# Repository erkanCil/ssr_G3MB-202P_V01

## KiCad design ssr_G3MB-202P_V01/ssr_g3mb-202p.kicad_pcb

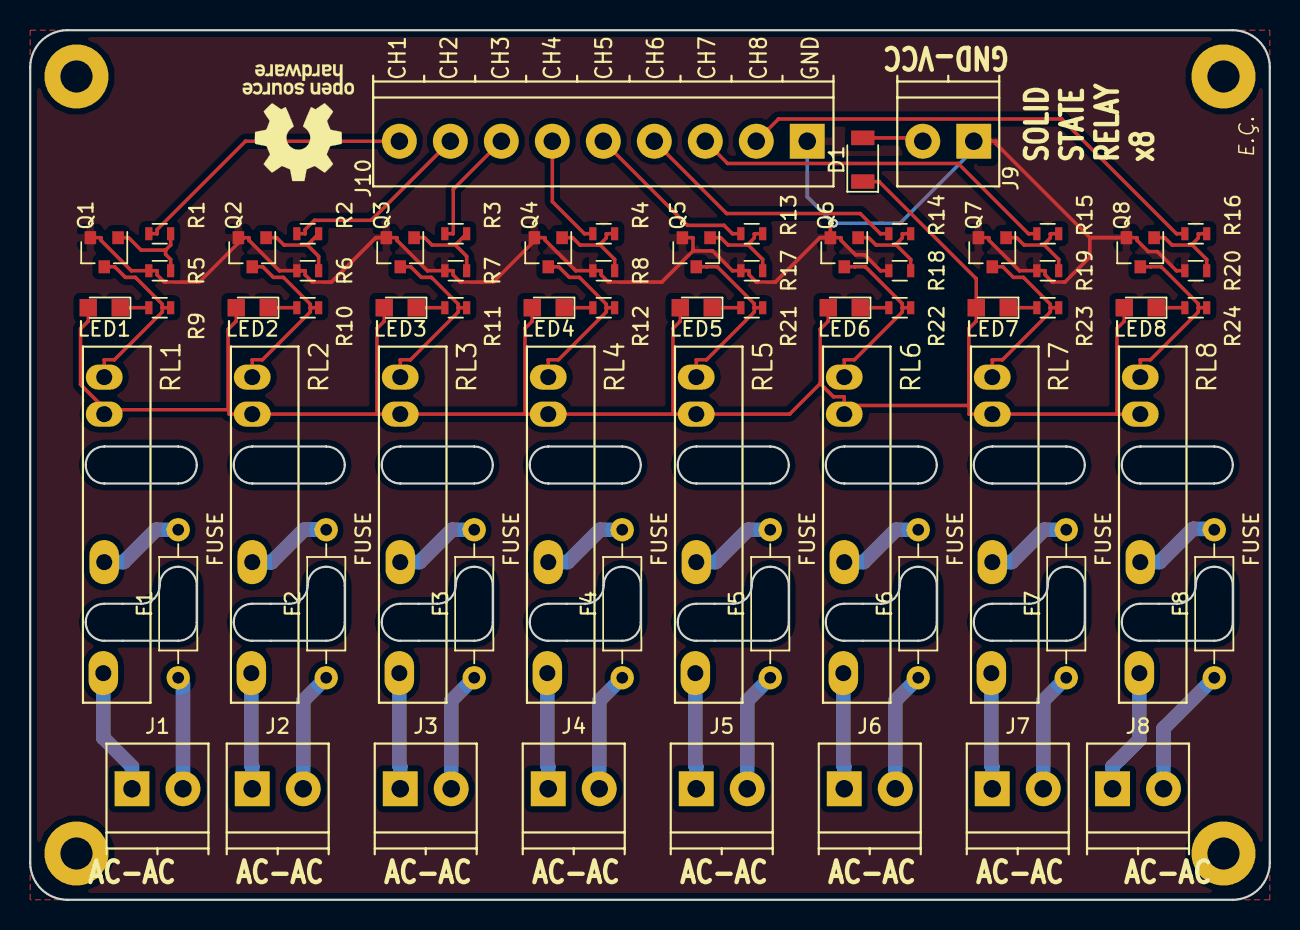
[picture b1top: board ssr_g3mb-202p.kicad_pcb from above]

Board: 2 copper layers, 85.1 x 59.7 mm, 71 parts (0 on the bottom side), 59 nets.

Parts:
D1: SM4001; D_1206
F1, F2, F3, F4, F5, F6, F7, F8: Fuse; R_Axial_DIN0207_L6.3mm_D2.5mm_P10.16mm_Horizontal
J1, J2, J3, J4, J5, J6, J7, J8, J9: Screw_Terminal_01x02; TerminalBlock_Pheonix_PT-3.5mm_2pol
J10: Screw_Terminal_01x09; TerminalBlock_Pheonix_PT-3.5mm_9pol
LED1, LED2, LED3, LED4, LED5, LED6, LED7, LED8: LED; LED_0805
Q1, Q2, Q3, Q4, Q5, Q6, Q7, Q8: MMBT3904/SOT23; SOT-23
R1, R2, R3, R4, R13, R14, R15, R16: 3K3; R_0603
R5, R6, R7, R8, R17, R18, R19, R20: 10K; R_0603
R9, R10, R11, R12, R21, R22, R23, R24: 1K; R_0603
REF1, REF2, REF3, REF4: MountingHole_2.2mm_M2_Pad
RL1, RL2, RL3, RL4, RL5, RL6, RL7, RL8: SSR_G3MB-202P; G3MB-202P

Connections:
+5V: D1.1, LED1.2, LED2.2, LED3.2, LED4.2, LED5.2, LED6.2, LED7.2, LED8.2, RL1.3, RL2.3, RL3.3, RL4.3, RL5.3, RL6.3, RL7.3, RL8.3
/CH1: J10.9, R1.2
/CH2: J10.8, R2.2
/CH3: J10.7, R3.2
/CH4: J10.6, R4.2
/CH5: J10.5, R13.2
/CH6: J10.4, R14.2
/CH7: J10.3, R15.2
/CH8: J10.2, R16.2
/VCC: D1.2, J9.2
GND: J9.1, J10.1, Q1.2, Q2.2, Q3.2, Q4.2, Q5.2, Q6.2, Q7.2, Q8.2, R5.2, R6.2, R7.2, R8.2, R17.2, R18.2, R19.2, R20.2
unnamed: Q1.1, R1.1, R5.1
unnamed: Q2.1, R2.1, R6.1
unnamed: Q3.1, R3.1, R7.1
unnamed: Q4.1, R4.1, R8.1
unnamed: LED1.1, R9.1
unnamed: Q1.3, R9.2, RL1.4
unnamed: LED2.1, R10.1
unnamed: Q2.3, R10.2, RL2.4
unnamed: LED3.1, R11.1
unnamed: Q3.3, R11.2, RL3.4
unnamed: LED4.1, R12.1
unnamed: Q4.3, R12.2, RL4.4
unnamed: Q5.1, R13.1, R17.1
unnamed: Q6.1, R14.1, R18.1
unnamed: Q7.1, R15.1, R19.1
unnamed: Q8.1, R16.1, R20.1
unnamed: LED5.1, R21.1
unnamed: Q5.3, R21.2, RL5.4
unnamed: LED6.1, R22.1
unnamed: Q6.3, R22.2, RL6.4
unnamed: LED7.1, R23.1
unnamed: Q7.3, R23.2, RL7.4
unnamed: LED8.1, R24.1
unnamed: Q8.3, R24.2, RL8.4
unnamed: F1.1, J1.2
unnamed: F1.2, RL1.2
unnamed: F2.1, J2.2
unnamed: F2.2, RL2.2
unnamed: F3.1, J3.2
unnamed: F3.2, RL3.2
unnamed: F4.1, J4.2
unnamed: F4.2, RL4.2
unnamed: F5.1, J5.2
unnamed: F5.2, RL5.2
unnamed: F6.1, J6.2
unnamed: F6.2, RL6.2
unnamed: F7.1, J7.2
unnamed: F7.2, RL7.2
unnamed: F8.1, J8.2
unnamed: F8.2, RL8.2
unnamed: J1.1, RL1.1
unnamed: J2.1, RL2.1
unnamed: J3.1, RL3.1
unnamed: J4.1, RL4.1
unnamed: J5.1, RL5.1
unnamed: J6.1, RL6.1
unnamed: J7.1, RL7.1
unnamed: J8.1, RL8.1

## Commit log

2017-11-26 :lollipop: Added .gitattributes & .gitignore files
